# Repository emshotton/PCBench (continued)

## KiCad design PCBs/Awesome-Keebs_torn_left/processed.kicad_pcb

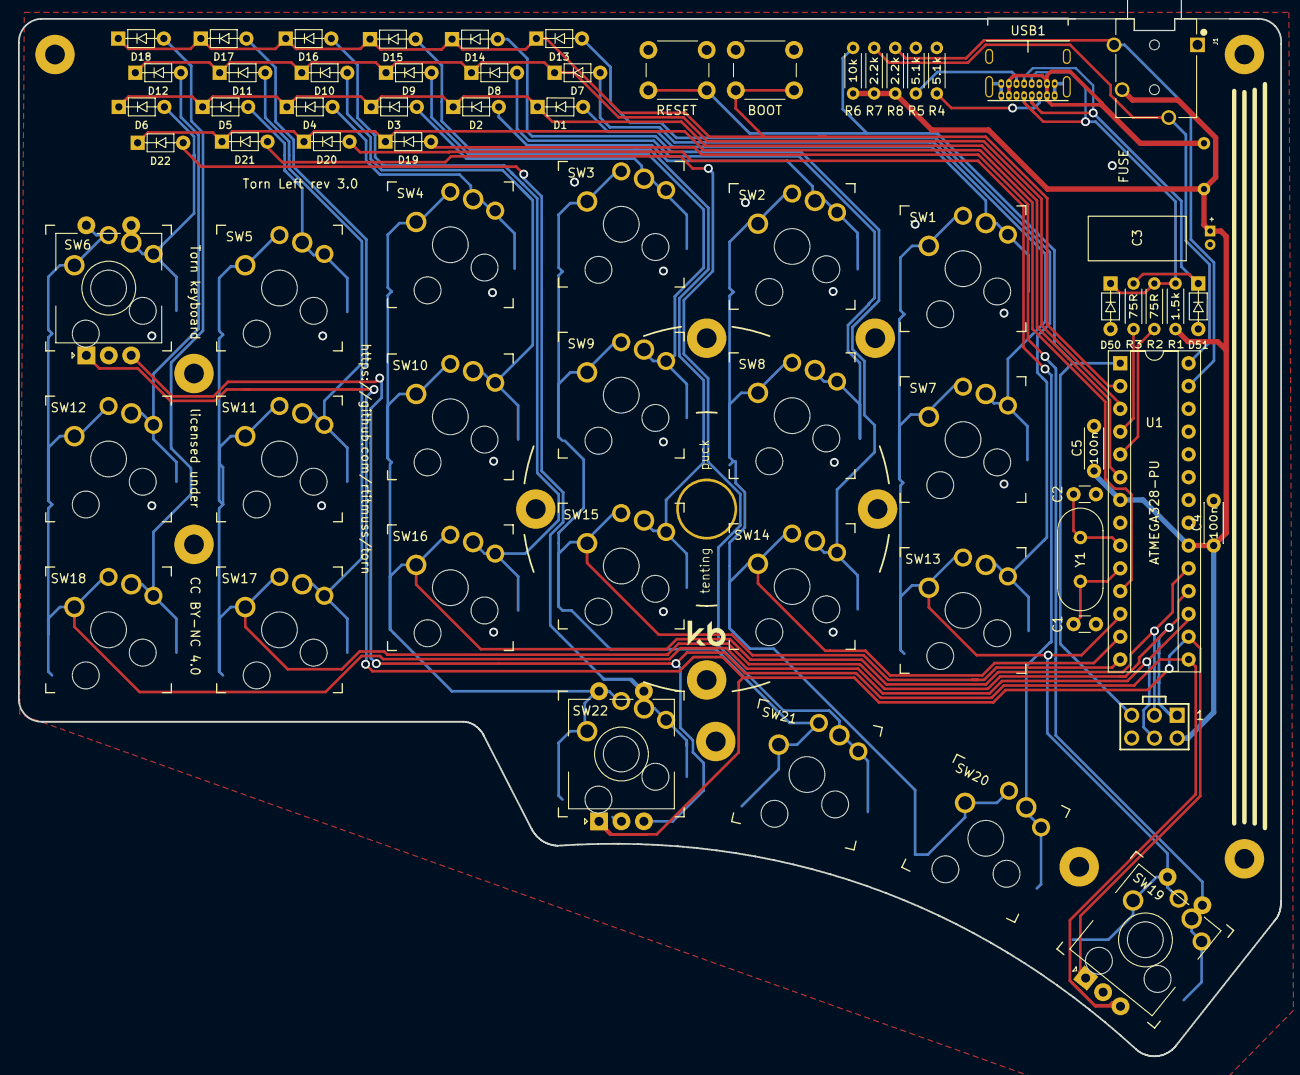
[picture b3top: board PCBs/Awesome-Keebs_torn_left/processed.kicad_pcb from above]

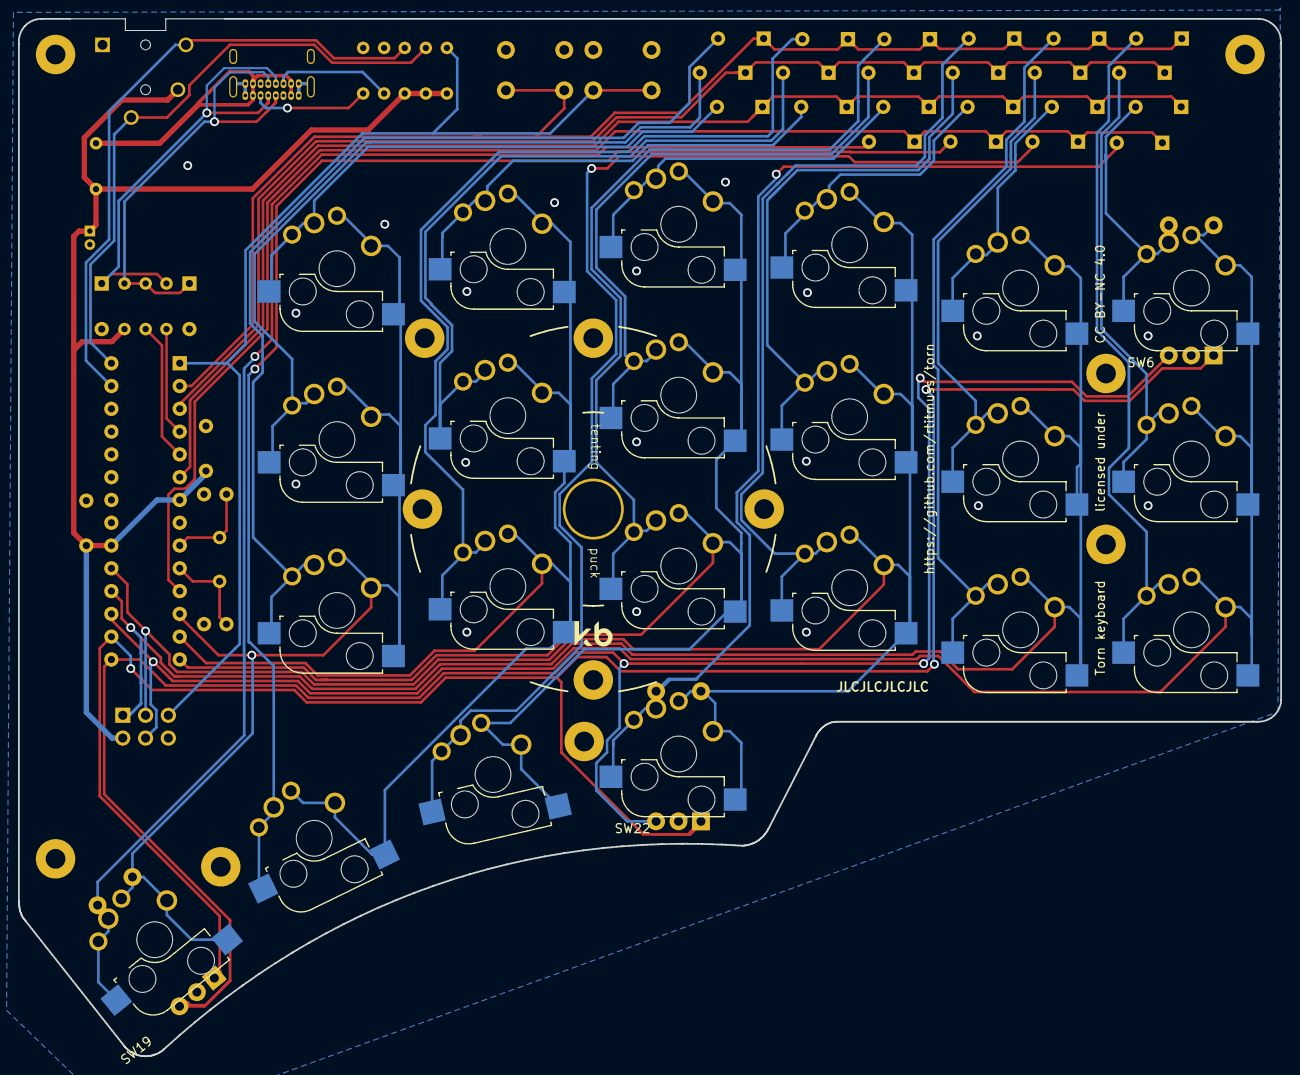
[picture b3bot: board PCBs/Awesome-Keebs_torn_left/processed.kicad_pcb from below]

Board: 2 copper layers, 140.7 x 115.6 mm, 76 parts (8 on the bottom side), 48 nets.

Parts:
C1, C2: 22p; C_Disc_D3.0mm_W1.6mm_P2.50mm
C3: 4.7u; CP_Radial_D4.0mm_P1.50mm
C4, C5: 100n; C_Disc_D4.3mm_W1.9mm_P5.00mm
D1, D2, D3, D4, D5, D6, D7, D8, D9, D10, D11, D12, D13, D14, D15, D16, D17, D18, D19, D20, D21, D22: 1N4148; D_DO-35_SOD27_P5.08mm_Horizontal
D50, D51: 3.6V; D_DO-35_SOD27_P5.08mm_Horizontal
F1: 100mA; polyfuse_5.1mm
H3, H4, H5, H6, H7, H8, H9, H10: M2; MountingHole_2.2mm_M2_Pad
ISP1: AVR_ISP_6; AVR_ICSP_3x2
J1: SJ-43514; CUI_SJ-43514
PB1: RESET; SW_PUSH_6mm
PB2: BOOT; SW_PUSH_6mm
PUCK1: SYM_Arrow45_Small; Tenting_Puck
R1: 1.5k; R_Axial_DIN0204_L3.6mm_D1.6mm_P5.08mm_Horizontal
R2, R3: 75R; R_Axial_DIN0204_L3.6mm_D1.6mm_P5.08mm_Horizontal
R4, R5: 5.1k; R_Axial_DIN0204_L3.6mm_D1.6mm_P5.08mm_Horizontal
R6: 10k; R_Axial_DIN0204_L3.6mm_D1.6mm_P5.08mm_Horizontal
R7, R8: 2.2k; R_Axial_DIN0204_L3.6mm_D1.6mm_P5.08mm_Horizontal
SW1, SW2, SW3, SW4, SW5, SW7, SW8, SW9, SW10, SW11, SW12, SW13, SW14, SW15, SW16, SW17, SW18, SW20, SW21: SW_Push; Kailh_socket_MX_PG1350_optional
SW6, SW19, SW22: Rotary_Encoder_Switch; Kailh_socket_MX_PG1350_EC11_optional
U1: ATMEGA328-PU; DIP-28_W7.62mm_Socket
USB1: USB_C_GCT_USB4085-Type-C; USB_C_GCT_USB4085
Y1: 16MHz; Crystal_HC49-4H_Vertical

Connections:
+5V: C3.1, C4.1, C5.1, F1.2, ISP1.2, J1.2, R1.2, R6.1, R7.1, R8.1, U1.7, U1.20
/COL0: SW1.2, SW7.2, SW13.2, SW19.S2, U1.12
/COL1: SW2.2, SW8.2, SW14.2, SW20.2, U1.13
/COL2: SW3.2, SW9.2, SW15.2, SW21.2, U1.14
/COL3: ISP1.3, SW4.2, SW10.2, SW16.2, SW22.S2, U1.19
/COL4: ISP1.1, SW5.2, SW11.2, SW17.2, U1.18
/COL5: ISP1.4, SW6.S2, SW12.2, SW18.2, U1.17
/ENC0_A: SW6.A, SW19.A, SW22.A, U1.16
/ENC0_B: SW6.B, SW19.B, SW22.B, U1.15
/RESET: ISP1.5, PB1.1, R6.2, U1.1
/ROW0: D1.1, D2.1, D3.1, D4.1, D5.1, D6.1, U1.6
/ROW1: D7.1, D8.1, D9.1, D10.1, D11.1, D12.1, U1.3
/ROW2: D13.1, D14.1, D15.1, D16.1, D17.1, D18.1, PB2.2, U1.2
/ROW3: D19.1, D20.1, D21.1, D22.1, U1.11
/USB_D+: R3.1, U1.4
/USB_D-: R2.1, U1.5
/i2c_SCL: J1.3, R7.2, U1.28
/i2c_SDA: J1.4, R8.2, U1.27
GND: C1.2, C2.2, C3.2, C4.2, C5.2, D50.2, D51.2, ISP1.6, J1.1, PB1.2, PB2.1, R4.1, R5.1, SW6.C, SW19.C, SW22.C, U1.8, U1.22, USB1.A1, USB1.A12, USB1.B1, USB1.B12, USB1.S1
unnamed: C1.1, U1.10, Y1.2
unnamed: C2.1, U1.9, Y1.1
unnamed: D1.2, SW1.1
unnamed: D2.2, SW2.1
unnamed: D3.2, SW3.1
unnamed: D4.2, SW4.1
unnamed: D5.2, SW5.1
unnamed: D6.2, SW6.S1
unnamed: D7.2, SW7.1
unnamed: D8.2, SW8.1
unnamed: D9.2, SW9.1
unnamed: D10.2, SW10.1
unnamed: D11.2, SW11.1
unnamed: D12.2, SW12.1
unnamed: D13.2, SW13.1
unnamed: D14.2, SW14.1
unnamed: D15.2, SW15.1
unnamed: D16.2, SW16.1
unnamed: D17.2, SW17.1
unnamed: D18.2, SW18.1
unnamed: D19.2, SW19.S1
unnamed: D20.2, SW20.1
unnamed: D21.2, SW21.1
unnamed: D22.2, SW22.S1
unnamed: D50.1, R1.1, R2.2, USB1.A7, USB1.B7
unnamed: D51.1, R3.2, USB1.A6, USB1.B6
unnamed: F1.1, USB1.A4, USB1.A9, USB1.B4, USB1.B9
unnamed: R4.2, USB1.A5
unnamed: R5.2, USB1.B5

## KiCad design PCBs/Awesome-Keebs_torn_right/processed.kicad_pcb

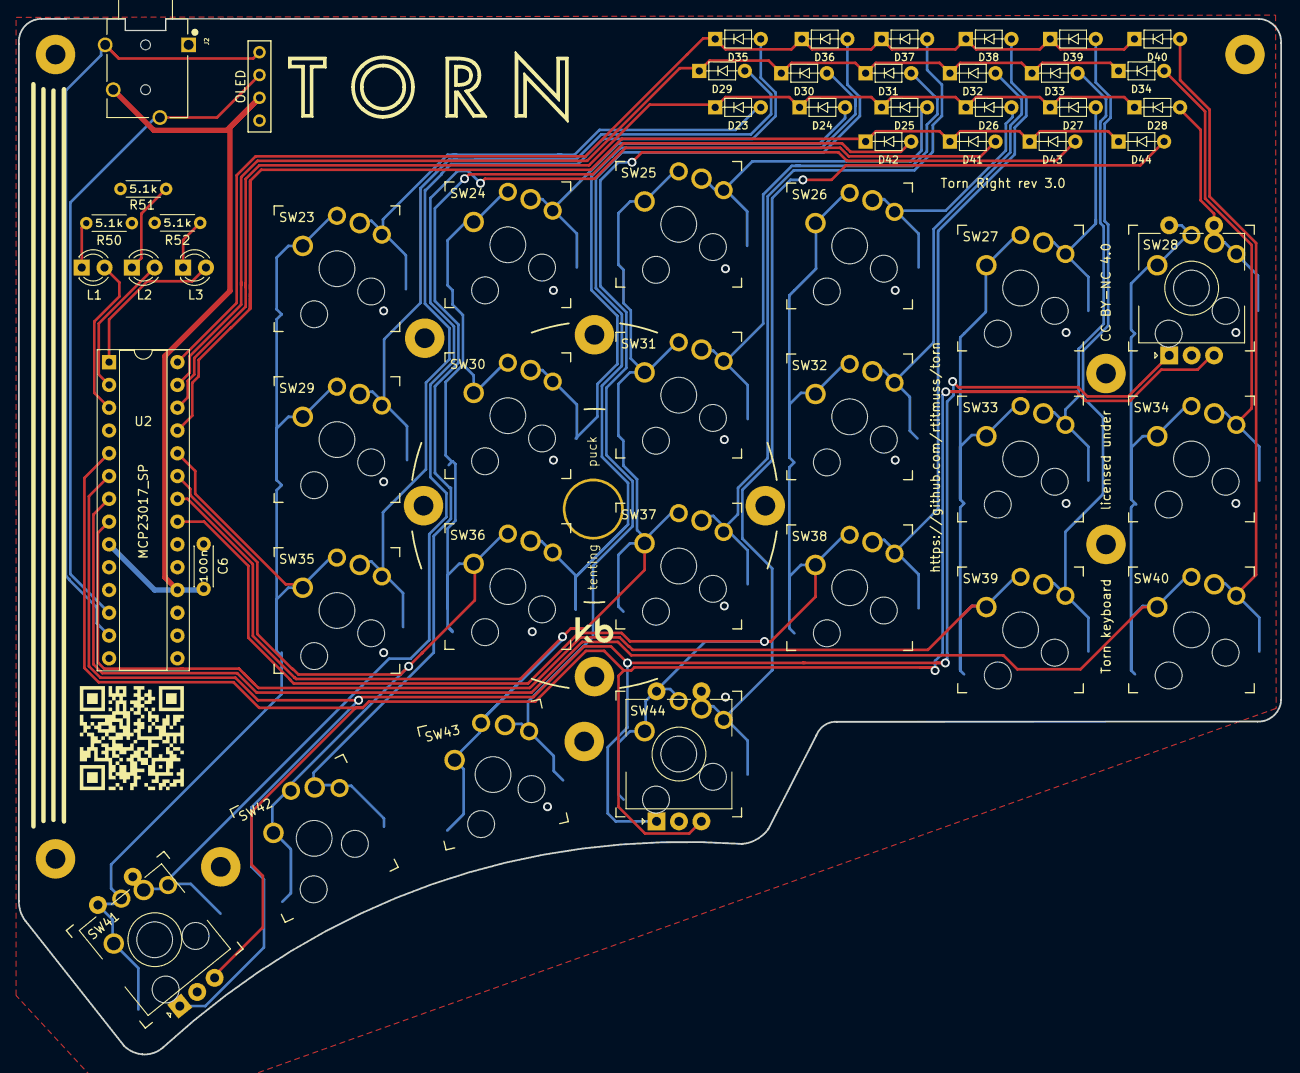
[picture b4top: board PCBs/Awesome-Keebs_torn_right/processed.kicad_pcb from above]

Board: 2 copper layers, 140.7 x 115.4 mm, 64 parts (0 on the bottom side), 44 nets.

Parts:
C6: 100n; C_Disc_D4.3mm_W1.9mm_P5.00mm
D23, D24, D25, D26, D27, D28, D29, D30, D31, D32, D33, D34, D35, D36, D37, D38, D39, D40, D41, D42, D43, D44: 1N4148; D_DO-35_SOD27_P5.08mm_Horizontal
H3, H4, H5, H6, H7, H8, H9, H10: M2; MountingHole_2.2mm_M2_Pad
J2: SJ-43514; CUI_SJ-43514
J3: Conn_01x04; OLED_1side
L1, L2, L3: LED; LED_D3.0mm
PUCK1: PUCK; Tenting_Puck
QR1: SYM_Arrow45_Small; torn_qr_code
R50, R51, R52: 5.1k; R_Axial_DIN0204_L3.6mm_D1.6mm_P5.08mm_Horizontal
SW23, SW24, SW25, SW26, SW27, SW29, SW30, SW31, SW32, SW33, SW34, SW35, SW36, SW37, SW38, SW39, SW40, SW42, SW43: SW_Push; Kailh_socket_MX_PG1350_optional
SW28, SW41, SW44: Rotary_Encoder_Switch; Kailh_socket_MX_PG1350_EC11_optional
U2: MCP23017_SP; DIP-28_W7.62mm_Socket

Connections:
+5V: C6.1, J2.2, J3.2, U2.9, U2.18
/COL6: SW23.2, SW29.2, SW35.2, SW41.S2, U2.24
/COL7: SW24.2, SW30.2, SW36.2, SW42.2, U2.23
/COL8: SW25.2, SW31.2, SW37.2, SW43.2, U2.22
/COL9: SW26.2, SW32.2, SW38.2, SW44.S2, U2.21
/COL10: SW27.2, SW33.2, SW39.2, U2.8
/COL11: SW28.S2, SW34.2, SW40.2, U2.7
/ENC1_A: SW28.A, SW41.A, SW44.A, U2.6
/ENC1_B: SW28.B, SW41.B, SW44.B, U2.5
/LED1: L1.2, U2.3
/LED2: L2.2, U2.2
/LED3: L3.2, U2.1
/ROW0: D23.1, D24.1, D25.1, D26.1, D27.1, D28.1, U2.26
/ROW1: D29.1, D30.1, D31.1, D32.1, D33.1, D34.1, U2.27
/ROW2: D35.1, D36.1, D37.1, D38.1, D39.1, D40.1, U2.28
/ROW3: D41.1, D42.1, D43.1, D44.1, U2.25
/i2c_SCL: J2.3, J3.3, U2.12
/i2c_SDA: J2.4, J3.4, U2.13
GND: C6.2, J2.1, J3.1, R50.1, R51.1, R52.1, SW28.C, SW41.C, SW44.C, U2.10, U2.15, U2.16, U2.17
unnamed: D23.2, SW23.1
unnamed: D24.2, SW24.1
unnamed: D25.2, SW25.1
unnamed: D26.2, SW26.1
unnamed: D27.2, SW27.1
unnamed: D28.2, SW28.S1
unnamed: D29.2, SW29.1
unnamed: D30.2, SW30.1
unnamed: D31.2, SW31.1
unnamed: D32.2, SW32.1
unnamed: D33.2, SW33.1
unnamed: D34.2, SW34.1
unnamed: D35.2, SW35.1
unnamed: D36.2, SW36.1
unnamed: D37.2, SW37.1
unnamed: D38.2, SW38.1
unnamed: D39.2, SW39.1
unnamed: D40.2, SW40.1
unnamed: D41.2, SW41.S1
unnamed: D42.2, SW42.1
unnamed: D43.2, SW43.1
unnamed: D44.2, SW44.S1
unnamed: L1.1, R50.2
unnamed: L2.1, R51.2
unnamed: L3.1, R52.2

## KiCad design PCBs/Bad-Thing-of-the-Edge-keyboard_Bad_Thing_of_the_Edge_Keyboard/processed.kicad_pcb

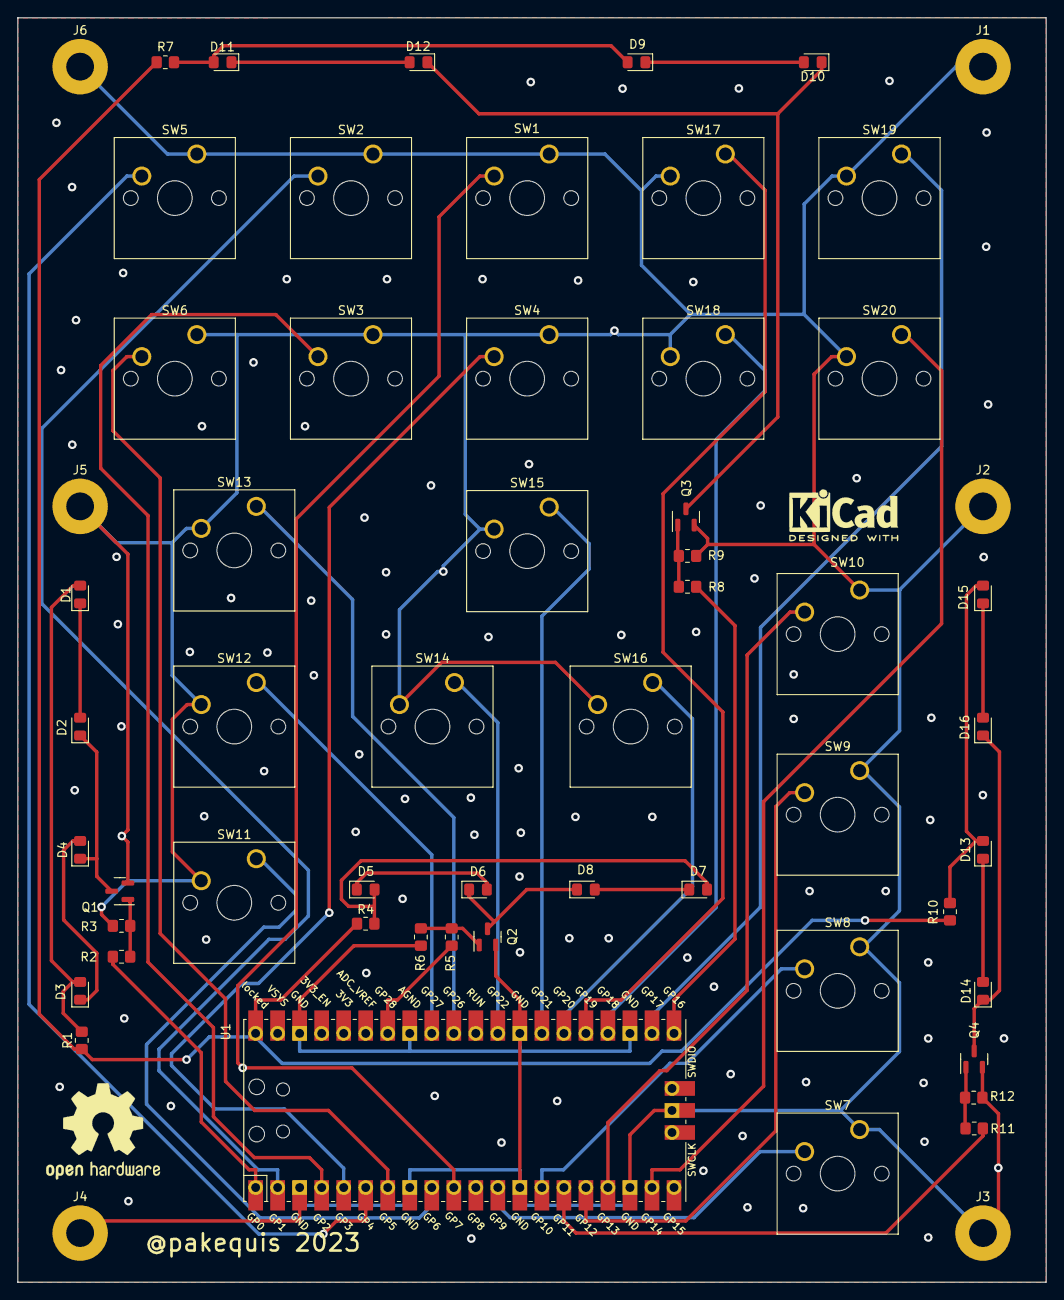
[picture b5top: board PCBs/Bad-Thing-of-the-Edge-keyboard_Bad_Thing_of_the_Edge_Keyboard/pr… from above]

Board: 2 copper layers, 118.6 x 145.8 mm, 61 parts (0 on the bottom side), 46 nets.

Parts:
D1, D2, D3, D4, D5, D6, D7, D8, D9, D10, D11, D12, D13, D14, D15, D16: LED; LED_0805_2012Metric_Pad1.15x1.40mm_HandSolder
J1, J2, J3, J4, J5, J6: Conn_01x01_Pin; MountingHole_3.2mm_M3_Pad
Q1, Q2, Q3, Q4: BSS138; SOT-23
R1, R4, R7, R10: 47R; R_0805_2012Metric_Pad1.20x1.40mm_HandSolder
R2, R5, R8, R11: 100R; R_0805_2012Metric_Pad1.20x1.40mm_HandSolder
R3, R6, R9, R12: 10k; R_0805_2012Metric_Pad1.20x1.40mm_HandSolder
SW1, SW2, SW3, SW4, SW5, SW6, SW7, SW8, SW9, SW10, SW11, SW12, SW13, SW14, SW15, SW16, SW17, SW18, SW19, SW20: SW_Push; SW_Cherry_MX_1.00u_PCB
U1: Pico; RPi_Pico_SMD_TH
m1: OSHW-Logo2_14.6x12mm_SilkScreen
m2: KiCad-Logo2_5mm_SilkScreen

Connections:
GNDREF: J1.1, J2.1, J3.1, J4.1, J5.1, J6.1, Q1.2 (S), Q2.2 (S), Q3.2 (S), Q4.2 (S), R3.2, R6.2, R9.2, R12.2, SW1.1, SW2.1, SW3.1, SW4.1, SW5.1, SW6.1, SW7.1, SW8.1, SW9.1, SW10.1, SW11.2, SW12.2, SW13.2, SW14.2, SW15.2, SW16.2, SW17.2, SW18.2, SW19.2, SW20.2, U1.3 (GND), U1.8 (GND), U1.13 (GND), U1.18 (GND), U1.23 (GND), U1.28 (GND), U1.33 (AGND), U1.38 (GND), U1.42 (GND)
unnamed: D1.2 (A), D3.2 (A), R1.2
unnamed: D1.1 (K), D2.2 (A)
unnamed: D2.1 (K), D4.1 (K), Q1.3 (D)
unnamed: D3.1 (K), D4.2 (A)
unnamed: D5.2 (A), D7.2 (A), R4.2
unnamed: D5.1 (K), D6.2 (A)
unnamed: D6.1 (K), D8.1 (K), Q2.3 (D)
unnamed: D7.1 (K), D8.2 (A)
unnamed: D9.1 (K), D10.2 (A)
unnamed: D10.1 (K), D12.1 (K), Q3.3 (D)
unnamed: D9.2 (A), D11.2 (A), R7.2
unnamed: D11.1 (K), D12.2 (A)
unnamed: D13.2 (A), D15.2 (A), R10.2
unnamed: D13.1 (K), D14.2 (A)
unnamed: D14.1 (K), D16.1 (K), Q4.3 (D)
unnamed: D15.1 (K), D16.2 (A)
unnamed: Q1.1 (G), R2.2, R3.1
unnamed: Q2.1 (G), R5.2, R6.1
unnamed: Q3.1 (G), R8.2, R9.1
unnamed: Q4.1 (G), R11.2, R12.1
unnamed: R2.1, U1.1 (GPIO0)
unnamed: SW2.2, U1.2 (GPIO1)
unnamed: SW3.2, U1.4 (GPIO2)
unnamed: SW4.2, U1.5 (GPIO3)
unnamed: SW5.2, U1.6 (GPIO4)
unnamed: SW6.2, U1.7 (GPIO5)
unnamed: SW11.1, U1.9 (GPIO6)
unnamed: SW1.2, U1.10 (GPIO7)
unnamed: SW7.2, U1.12 (GPIO9)
unnamed: SW8.2, U1.14 (GPIO10)
unnamed: R11.1, U1.15 (GPIO11)
unnamed: SW9.2, U1.16 (GPIO12)
unnamed: SW10.2, U1.17 (GPIO13)
unnamed: SW20.1, U1.19 (GPIO14)
unnamed: R8.1, U1.21 (GPIO16)
unnamed: SW19.1, U1.22 (GPIO17)
unnamed: SW18.1, U1.24 (GPIO18)
unnamed: SW17.1, U1.25 (GPIO19)
unnamed: SW16.1, U1.26 (GPIO20)
unnamed: SW15.1, U1.27 (GPIO21)
unnamed: SW14.1, U1.29 (GPIO22)
unnamed: SW13.1, U1.31 (GPIO26_ADC0)
unnamed: SW12.1, U1.32 (GPIO27_ADC1)
unnamed: R5.1, U1.34 (GPIO28_ADC2)
VBUS: R1.1, R4.1, R7.1, R10.1, U1.40 (VBUS)

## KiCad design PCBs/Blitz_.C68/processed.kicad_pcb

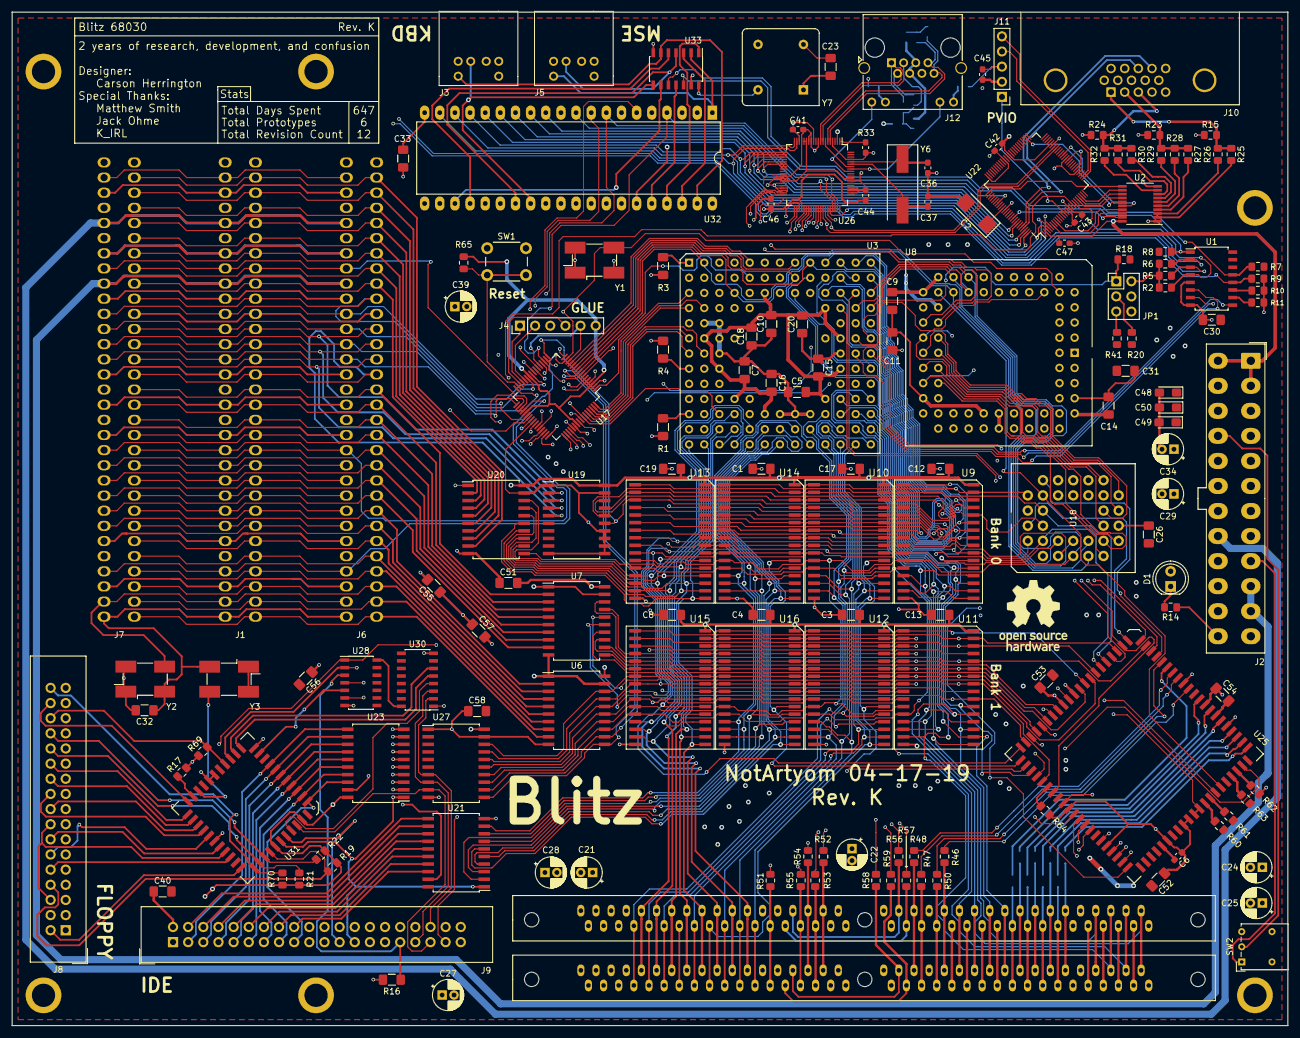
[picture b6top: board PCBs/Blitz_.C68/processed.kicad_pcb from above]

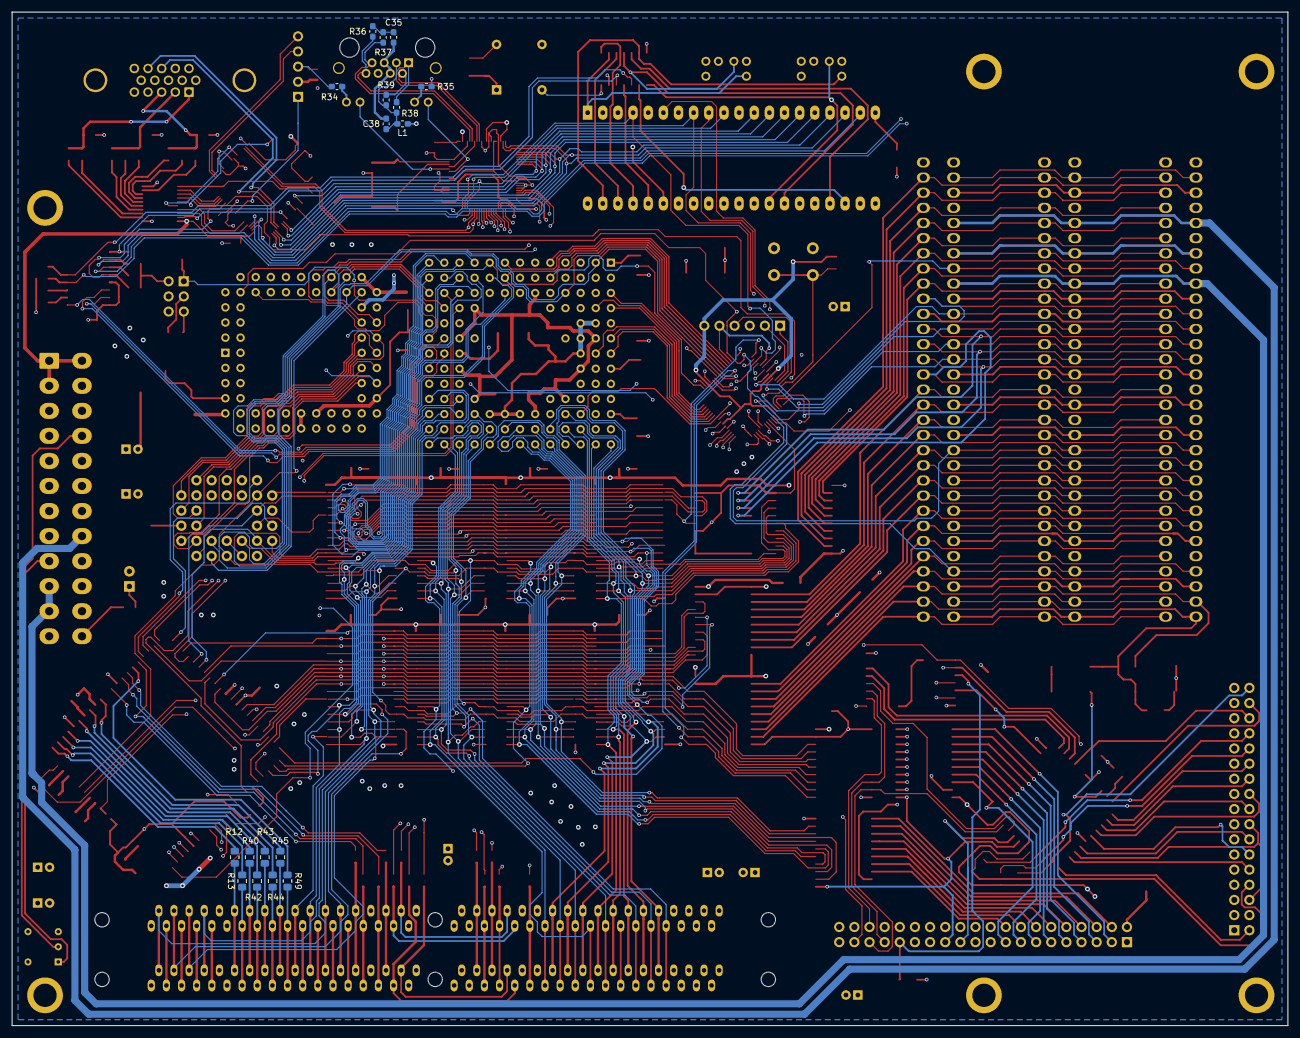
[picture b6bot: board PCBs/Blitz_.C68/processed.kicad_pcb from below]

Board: 4 copper layers, 214.0 x 170.0 mm, 184 parts (17 on the bottom side), 310 nets.

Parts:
C1, C3, C4, C5, C7, C8, C9, C10, C11, C12, C13, C14, C15, C16, C17, C18, C19, C20, C23, C26, C30, C31, C32, C33, C40, C51, C52, C53, C54, C55, C56, C57, C58: 100nf; C_1206_3216Metric_Pad1.42x1.75mm_HandSolder
C2: 10uf; CP_EIA-6032-20_AVX-F_Pad2.25x2.35mm_HandSolder
C6, C38, C41, C42, C43, C44, C45, C46, C47: 100nf; C_0603_1608Metric_Pad1.05x0.95mm_HandSolder
C21, C22, C24, C25, C27, C28, C29, C34: 47uf; CP_Radial_D5.0mm_P2.00mm
C35: 10nf; C_0603_1608Metric_Pad1.05x0.95mm_HandSolder
C36, C37: 10pf; C_0603_1608Metric_Pad1.05x0.95mm_HandSolder
C39: 10uf; CP_Radial_D5.0mm_P2.00mm
C48, C49, C50: 1uf; CP_EIA-3216-10_Kemet-I_Pad1.58x1.35mm_HandSolder
D1: LED; LED_D5.0mm
H1, H2, H3, H4, H5, H6: PTH_mount; atx_mounting_hole
J1, J6, J7: ISAx8; ISA_x8_VERT
J2: ATX24; Molex_Mini-Fit_Jr_5566-24A_2x12_P4.20mm_Vertical
J3: MSE; PS2
J4: PRG0; PinHeader_1x06_P2.54mm_Vertical
J5: KBD; PS2
J8: FLOPPY; IDC-Header_2x17_P2.54mm_Vertical
J9: IDE; IDC-Header_2x20_P2.54mm_Vertical
J10: VGA; Dsub-VGA
J11: ICSP; PinHeader_1x05_P2.54mm_Vertical
J12: RJ45_LED; RJ45_Amphenol_RJHSE538X
JP1: Conn_02x03_Odd_Even; PinHeader_2x03_P2.54mm_Vertical
L1: L; L_0603_1608Metric_Pad1.05x0.95mm_HandSolder
R1, R3, R4, R16: 10k; R_1206_3216Metric_Pad1.42x1.75mm_HandSolder
R2, R5, R6, R7, R8, R9, R10, R11, R14, R18, R20, R41, R65: 10k; R_0805_2012Metric_Pad1.15x1.40mm_HandSolder
R12, R13, R40, R42, R43, R44, R45, R46, R47, R48, R49, R50, R51, R52, R53, R54, R55, R56, R57, R58, R59: 22; R_0805_2012Metric_Pad1.15x1.40mm_HandSolder
R15, R23, R24: 75; R_0805_2012Metric_Pad1.15x1.40mm_HandSolder
R17, R19, R21, R22, R69, R70: 150; R_0805_2012Metric_Pad1.15x1.40mm_HandSolder
R25: 455; R_0805_2012Metric_Pad1.15x1.40mm_HandSolder
R26: 986; R_0805_2012Metric_Pad1.15x1.40mm_HandSolder
R27, R30: 544; R_0805_2012Metric_Pad1.15x1.40mm_HandSolder
R28, R31: 1k2; R_0805_2012Metric_Pad1.15x1.40mm_HandSolder
R29, R32: 2k4; R_0805_2012Metric_Pad1.15x1.40mm_HandSolder
R33: 12.3k; R_0603_1608Metric_Pad1.05x0.95mm_HandSolder
R34, R35: 330; R_0603_1608Metric_Pad1.05x0.95mm_HandSolder
R36, R37, R38, R39: 49k9; R_0603_1608Metric_Pad1.05x0.95mm_HandSolder
R60, R61, R62, R63, R64: 2k2; R_0805_2012Metric_Pad1.15x1.40mm_HandSolder
SW1: RESET; SW_PUSH_6mm
SW2: SW_SPDT; SW_Lever_1P2T_NKK_GW12LxH
U1: 74LS148; SOIC-16W_5.3x10.2mm_P1.27mm
U2: 74LVC245APW; TSSOP-20_4.4x6.5mm_P0.65mm
U3: M68030; PGA120
U5, U24: SIMM_72
U6, U7, U19, U20, U21, U23, U27: 74LS245; SOIC-20W_7.5x12.8mm_P1.27mm
U8: M68882_PLCC; PLCC-68_THT-Socket
U9, U10, U11, U12, U13, U14, U15, U16: AS6C4008; SOIC-32
U17: XC9572XL-VQ64; TQFP-64_10x10mm_P0.5mm
U18: SST39SF040; PLCC-32_TH
U22: PIC24FJ256DA210-IPT; TQFP-100_12x12mm_P0.4mm
U25: DP8440; PLCC-84
U26: W5100; LQFP-80_10x10mm_P0.4mm
U28: 7404; SOIC-14_3.9x8.7mm_P1.27mm
U30: 74hc139; SOIC-16_3.9x9.9mm_P1.27mm
U31: WD37C65; PLCC-44
U32: 8042; DIP-40_W15.24mm_LongPads
U33: 74LS06; SOIC-14_3.9x8.7mm_P1.27mm
Y1: 20MHz; Oscillator_SMD_EuroQuartz_XO91-4Pin_7.0x5.0mm_HandSoldering
Y2: 14.316MHz; Oscillator_SMD_EuroQuartz_XO91-4Pin_7.0x5.0mm_HandSoldering
Y3: 16MHz; Oscillator_SMD_EuroQuartz_XO91-4Pin_7.0x5.0mm_HandSoldering
Y6: 25MHz; Crystal_SMD_HC49-SD
Y7: 8MHz; Oscillator_DIP-8

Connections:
!READ: J9.25, U17.56, U18.24, U21.1, U23.1, U26.58, U31.1, U32.8
+3V3: C41.2, C42.2, C43.2, C44.2, C45.2, C46.2, C47.2, J2.1, J2.2, J2.12, J2.13, J4.6, J11.2, L1.2, R65.1, U2.20, U17.3, U17.26, U17.37, U17.55, U22.2, U22.16, U22.30, U22.37, U22.46, U22.62, U22.86, U26.2, U26.12, U26.18, U26.44
+5V: C1.2, C3.2, C4.2, C5.2, C7.2, C8.2, C9.2, C10.2, C11.2, C12.2, C13.2, C14.2, C15.2, C16.2, C17.2, C18.2, C19.2, C20.2, C21.1, C22.1, C23.2, C24.1, C25.1, C26.2, C27.1, C28.1, C29.1, C30.2, C31.2, C32.2, C33.2, C34.1, C39.1, C40.2, C48.1, C49.1, C50.1, C51.2, C52.2, C53.2, C54.2, C55.2, C56.2, C57.2, C58.2, D1.2, J1.B3, J1.B15, J1.B17, J1.B19, J1.B26, J1.B29, J2.4, J2.6, J2.21, J2.22, J2.23, J3.4, J5.4, J6.B3, J6.B15, J6.B17, J6.B19, J6.B26, J6.B29, J7.B3, J7.B15, J7.B17, J7.B19, J7.B26, J7.B29, J9.29, J9.38, R1.1, R3.1, R4.1, R7.1, R8.1, R17.2, R18.1, R19.2, R20.1, R21.2, R22.2, R41.1, R60.1, R61.1, R63.1, R69.2, R70.2, U1.16, U3.C6, U3.D4, U3.D10, U3.F2, U3.F11, U3.H3, U3.H11, U3.K4, U3.K10, U3.L6, U5.10, U5.30, U5.59, U6.20, U7.20, U8.10, U8.16, U8.17, U8.18, U8.26, U8.27, U8.43, U8.52, U8.53, U8.61, U9.32, U10.32, U11.32, U12.32, U13.32, U14.32, U15.32, U16.32, U18.32, U19.20, U20.20, U21.20, U23.20, U24.10, U24.30, U24.59, U25.1, U25.22, U25.40, U25.47, U25.57, U25.61, U25.81, U27.20, U28.14, U30.16, U31.5, U31.44, U32.5, U32.25, U32.26, U32.40, U33.14, Y1.1, Y1.4, Y2.1, Y2.4, Y3.1, Y3.4, Y7.1, Y7.8
+12V: J1.B9, J2.10, J2.11, J6.B9, J7.B9
-5V: J1.B5, J2.20, J6.B5, J7.B5
-12V: J1.B7, J2.14, J6.B7, J7.B7
/A0: U3.A2, U6.11, U17.8, U18.12, U22.44, U26.54, U27.11, U32.9
/A1: U3.C4, U6.12, U8.25, U17.9, U18.11, U22.43, U26.53, U27.12
/A2: U3.D13, U6.13, U8.24, U9.12, U10.12, U11.12, U12.12, U13.12, U14.12, U15.12, U16.12, U18.10, U25.9, U26.52, U27.13
/A3: U3.D12, U6.14, U8.23, U9.11, U10.11, U11.11, U12.11, U13.11, U14.11, U15.11, U16.11, U18.9, U25.11, U26.51, U27.14
/A4: U3.C13, U6.15, U8.22, U9.10, U10.10, U11.10, U12.10, U13.10, U14.10, U15.10, U16.10, U18.8, U25.13, U25.39, U26.50, U27.15
/A5: U3.C12, U6.16, U9.9, U10.9, U11.9, U12.9, U13.9, U14.9, U15.9, U16.9, U18.7, U25.15, U26.49, U27.16
/A6: U3.D11, U6.17, U9.8, U10.8, U11.8, U12.8, U13.8, U14.8, U15.8, U16.8, U18.6, U25.17, U26.48, U27.17
/A7: U3.B13, U6.18, U9.7, U10.7, U11.7, U12.7, U13.7, U14.7, U15.7, U16.7, U18.5, U25.19, U26.47, U27.18
/A8: U3.B12, U7.11, U9.6, U10.6, U11.6, U12.6, U13.6, U14.6, U15.6, U16.6, U18.27, U25.21, U26.46
/A9: U3.C11, U7.12, U9.5, U10.5, U11.5, U12.5, U13.5, U14.5, U15.5, U16.5, U18.26, U25.25, U26.45
/A10: U3.A13, U7.13, U9.27, U10.27, U11.27, U12.27, U13.27, U14.27, U15.27, U16.27, U18.23, U25.27, U26.42
/A11: U3.C10, U7.14, U9.26, U10.26, U11.26, U12.26, U13.26, U14.26, U15.26, U16.26, U18.25, U25.29, U26.41
/A12: U3.B11, U7.15, U9.23, U10.23, U11.23, U12.23, U13.23, U14.23, U15.23, U16.23, U18.4, U25.31, U26.40
/A13: U3.A12, U7.16, U9.25, U10.25, U11.25, U12.25, U13.25, U14.25, U15.25, U16.25, U18.28, U25.37, U26.39
/A14: U3.B10, U7.17, U9.4, U10.4, U11.4, U12.4, U13.4, U14.4, U15.4, U16.4, U18.29, U25.8, U26.38
/A15: U3.A11, U7.18, U9.28, U10.28, U11.28, U12.28, U13.28, U14.28, U15.28, U16.28, U18.3, U25.10
/A16: U3.B9, U9.3, U10.3, U11.3, U12.3, U13.3, U14.3, U15.3, U16.3, U17.17, U18.2, U19.15, U25.12
/A17: U3.A10, U9.31, U10.31, U11.31, U12.31, U13.31, U14.31, U15.31, U16.31, U18.30, U19.16, U25.14
/A18: U3.C8, U9.2, U10.2, U11.2, U12.2, U13.2, U14.2, U15.2, U16.2, U18.1, U19.17, U25.16
/A19: U3.A9, U9.30, U10.30, U11.30, U12.30, U13.30, U14.30, U15.30, U16.30, U17.10, U19.18, U25.18
/A20: U3.B8, U9.1, U10.1, U11.1, U12.1, U13.1, U14.1, U15.1, U16.1, U17.11, U25.20
/A21: U3.A8, U17.12, U25.23
/A22: U3.B7, U25.26
/A23: U3.A7, U25.28
/A24: U3.A6, U25.30
/A25: U3.B6, U25.36
/A26: U3.A5, U17.13
/A27: U3.B5, U17.1
/B0: R30.2, U2.7
/B1: R31.2, U2.8
/B2: R32.2, U2.9
/CAS0: R52.1, U5.40, U24.40
/CAS1: R53.1, U5.41, U24.41
/CAS2: R54.1, U5.42, U24.42
/CAS3: R55.1, U5.43, U24.43
/D0: U3.K13, U5.2, U8.3, U9.13, U11.13, U24.2
/D1: U3.K12, U5.4, U8.2, U9.14, U11.14, U24.4
/D2: U3.L13, U5.6, U8.1, U9.15, U11.15, U24.6
/D3: U3.M13, U5.8, U8.68, U9.17, U11.17, U24.8
/D4: U3.L12, U5.20, U8.67, U9.18, U11.18, U24.20
/D5: U3.K11, U5.22, U8.66, U9.19, U11.19, U24.22
/D6: U3.M12, U5.24, U8.65, U9.20, U11.20, U24.24
/D7: U3.L11, U5.26, U8.64, U9.21, U11.21, U24.26
/D8: U3.N13, U5.49, U8.62, U10.13, U12.13, U24.49
/D9: U3.M11, U5.51, U8.60, U10.14, U12.14, U24.51
/D10: U3.L10, U5.53, U8.59, U10.15, U12.15, U24.53
/D11: U3.N12, U5.55, U8.58, U10.17, U12.17, U24.55
/D12: U3.M10, U5.57, U8.57, U10.18, U12.18, U24.57
/D13: U3.N11, U5.61, U8.56, U10.19, U12.19, U24.61
/D14: U3.M9, U5.63, U8.55, U10.20, U12.20, U24.63
/D15: U3.N10, U5.65, U8.54, U10.21, U12.21, U24.65
/D16: U3.N9, U5.3, U8.50, U14.13, U16.13, U21.9, U24.3
/D17: U3.M8, U5.5, U8.49, U14.14, U16.14, U21.8, U24.5
/D18: U3.N8, U5.7, U8.48, U14.15, U16.15, U21.7, U24.7
/D19: U3.N7, U5.9, U8.47, U14.17, U16.17, U21.6, U24.9
/D20: U3.M7, U5.21, U8.46, U14.18, U16.18, U21.5, U24.21
/D21: U3.N6, U5.23, U8.45, U14.19, U16.19, U21.4, U24.23
/D22: U3.M6, U5.25, U8.44, U14.20, U16.20, U21.3, U24.25
/D23: U3.N5, U5.27, U8.42, U14.21, U16.21, U21.2, U24.27
/D24: U3.M5, U5.50, U8.40, U13.13, U15.13, U18.13, U20.18, U22.93, U23.2, U24.50, U26.26, U32.12
/D25: U3.N4, U5.52, U8.39, U13.14, U15.14, U18.14, U20.17, U22.94, U23.3, U24.52, U26.25, U32.13
/D26: U3.N3, U5.54, U8.38, U13.15, U15.15, U18.15, U20.16, U22.98, U23.4, U24.54, U26.24, U32.14
/D27: U3.M4, U5.56, U8.37, U13.17, U15.17, U18.17, U20.15, U22.99, U23.5, U24.56, U26.23, U32.15
/D28: U3.N2, U5.58, U8.36, U13.18, U15.18, U18.18, U20.14, U22.100, U23.6, U24.58, U26.22, U32.16
/D29: U3.M3, U5.60, U8.35, U13.19, U15.19, U18.19, U20.13, U22.3, U23.7, U24.60, U26.21, U32.17
/D30: U3.L4, U5.62, U8.34, U13.20, U15.20, U18.20, U20.12, U22.4, U23.8, U24.62, U26.20, U32.18
/D31: U3.N1, U5.64, U8.33, U13.21, U15.21, U18.21, U20.11, U22.5, U23.9, U24.64, U26.19, U32.19
/G0: R27.2, U2.4
/G1: R28.2, U2.5
/G2: R29.2, U2.6
/IA0: J1.A31, J6.A31, J7.A31, U6.9
/IA1: J1.A30, J6.A30, J7.A30, U6.8
/IA2: J1.A29, J6.A29, J7.A29, U6.7
/IA3: J1.A28, J6.A28, J7.A28, U6.6
/IA4: J1.A27, J6.A27, J7.A27, U6.5
/IA5: J1.A26, J6.A26, J7.A26, U6.4
/IA6: J1.A25, J6.A25, J7.A25, U6.3
/IA7: J1.A24, J6.A24, J7.A24, U6.2
/IA8: J1.A23, J6.A23, J7.A23, U7.9
/IA9: J1.A22, J6.A22, J7.A22, U7.8
/IA10: J1.A21, J6.A21, J7.A21, U7.7
/IA11: J1.A20, J6.A20, J7.A20, U7.6
/IA12: J1.A19, J6.A19, J7.A19, U7.5
/IA13: J1.A18, J6.A18, J7.A18, U7.4
/IA14: J1.A17, J6.A17, J7.A17, U7.3
/IA15: J1.A16, J6.A16, J7.A16, U7.2
/IA16: J1.A15, J6.A15, J7.A15, U19.5
/IA17: J1.A14, J6.A14, J7.A14, U19.4
/IA18: J1.A13, J6.A13, J7.A13, U19.3
/IA19: J1.A12, J6.A12, J7.A12, U19.2
/ID0: J1.A9, J6.A9, J7.A9, U20.2
/ID1: J1.A8, J6.A8, J7.A8, U20.3
/ID2: J1.A7, J6.A7, J7.A7, U20.4
/ID3: J1.A6, J6.A6, J7.A6, U20.5
/ID4: J1.A5, J6.A5, J7.A5, U20.6
/ID5: J1.A4, J6.A4, J7.A4, U20.7
/ID6: J1.A3, J6.A3, J7.A3, U20.8
/ID7: J1.A2, J6.A2, J7.A2, U20.9
/IOA0: J9.35, U27.9, U31.4
/IOA1: J9.33, U27.8, U30.3
/IOA2: J9.36, U27.7, U30.2
/IOD16: J9.4, U21.11
/IOD17: J9.6, U21.12
/IOD18: J9.8, U21.13
/IOD19: J9.10, U21.14
/IOD20: J9.12, U21.15
/IOD21: J9.14, U21.16
/IOD22: J9.16, U21.17
/IOD23: J9.18, U21.18
/IOD24: J9.17, U23.18, U31.7
/IOD25: J9.15, U23.17, U31.8
/IOD26: J9.13, U23.16, U31.9
/IOD27: J9.11, U23.15, U31.10
/IOD28: J9.9, U23.14, U31.11
/IOD29: J9.7, U23.13, U31.12
/IOD30: J9.5, U23.12, U31.13
/IOD31: J9.3, U23.11, U31.14
/QA0: R12.1, U5.12, U24.12
/QA1: R13.1, U5.13, U24.13
/QA2: R40.1, U5.14, U24.14
/QA3: R42.1, U5.15, U24.15
/QA4: R43.1, U5.16, U24.16
/QA5: R44.1, U5.17, U24.17
/QA6: R45.1, U5.18, U24.18
/QA7: R46.1, U5.28, U24.28
/QA8: R47.1, U5.31, U24.31
/QA9: R48.1, U5.32, U24.32
/QA10: R49.1, U5.19, U24.19
/QA11: R50.1, U5.29, U24.29
/R0: R25.2, U2.2
/R1: R26.2, U2.3
/RAS0: R56.1, U5.34, U5.44
/RAS1: R57.1, U5.33, U5.45
/RAS2: R58.1, U24.34, U24.44
/RAS3: R59.1, U24.33, U24.45
/RXI+: J12.7, R37.2, U26.5
/RXI-: J12.8, R36.1, U26.6
/TXO+: J12.1, R38.2, U26.8
/TXO-: J12.2, R39.1, U26.9
AS: U3.J2, U8.21, U17.2
BYTE0: U9.22, U11.22, U17.52, U25.35
BYTE1: U10.22, U12.22, U17.51, U25.34
BYTE2: U14.22, U16.22, U17.50, U25.33
BYTE3: U13.22, U15.22, U17.49, U25.32
CDIS: U3.H12, U17.23
CLK: J1.B20, J6.B20, J7.B20, U3.E1, U8.11, U17.15, U25.64, U25.65, Y1.3
DRAM_CS: U17.42, U25.53
DRAM_DTACK: U17.34, U25.73
DS: U3.K2, U8.20, U17.4
DSACK0: U3.F1, U8.31, U17.60
DSACK1: U3.G2, U8.32, U17.61
ECS: U3.M2, U17.18
ETHRNT: U17.43, U26.55
FC0: U3.D2, U17.63
FC1: U3.C1, U17.64
FC2: U3.D1, U17.62
FLOPPY: U17.20, U30.1
FPU: U8.29, U17.57
GEN: U2.19, U22.91
GND: C1.1, C2.2, C3.1, C4.1, C5.1, C6.1, C7.1, C8.1, C9.1, C10.1, C11.1, C12.1, C13.1, C14.1, C15.1, C16.1, C17.1, C18.1, C19.1, C20.1, C21.2, C22.2, C23.1, C24.2, C25.2, C26.1, C27.2, C28.2, C29.2, C30.1, C31.1, C32.1, C33.1, C34.2, C35.2, C36.2, C37.2, C38.2, C39.2, C40.1, C41.1, C42.1, C43.1, C44.1, C45.1, C46.1, C47.1, C48.2, C49.2, C50.2, C51.1, C52.1, C53.1, C54.1, C55.1, C56.1, C57.1, C58.1, H1.1, H2.1, H3.1, H4.1, H5.1, H6.1, J1.A11, J1.B1, J1.B10, J1.B31, J2.3, J2.5, J2.7, J2.15, J2.17, J2.18, J2.19, J2.24, J3.3, J4.5, J5.3, J6.A11, J6.B1, J6.B10, J6.B31, J7.A11, J7.B1, J7.B10, J7.B31, J8.1, J8.3, J8.5, J8.7, J8.9, J8.11, J8.13, J8.15, J8.17, J8.19, J8.21, J8.23, J8.25, J8.27, J8.29, J8.31, J8.33, J9.2, J9.19, J9.22, J9.24, J9.26, J9.28, J9.30, J9.40, J10.0, J10.5, J10.6, J10.7, J10.8, J10.10, J11.3, J12.4, J12.5, JP1.2, JP1.4, JP1.6, R2.1, R5.1, R6.1, R9.1, R10.1, R11.1, R14.1, R15.2, R16.1, R23.2, R24.2, R33.1, R34.1, R35.1, R62.1, R64.1, SW1.1, SW2.3, U1.5, U1.8, U2.1, U2.10, U3.C5, U3.C7, U3.C9, U3.E2, U3.E3, U3.E11, U3.F3, U3.G3, U3.G11, U3.J3, U3.J11, U3.L5, U3.L7, U3.L8, U3.L9, U5.1, U5.39, U5.72, U6.1, U6.10, U6.19, U7.1, U7.10, U7.19, U8.5, U8.6, U8.7, U8.8, U8.9, U8.12, U8.14, U8.19, U8.30, U8.41, U8.51, U8.63, U9.16, U10.16, U11.16, U12.16, U13.16, U14.16, U15.16, U16.16, U17.14, U17.21, U17.41, U17.54, U18.16, U19.1, U19.10, U19.11, U19.12, U19.13, U19.14, U19.19, U20.10, U20.19, U21.10, U22.15, U22.31, U22.36, U22.45, U22.65, U22.75, U23.10, U24.1, U24.39, U24.72, U25.3, U25.24, U25.42, U25.49, U25.59, U25.62, U25.63, U25.79, U25.83, U26.4, U26.10, U26.13, U26.14, U26.17, U26.31, U26.32, U26.34, U26.35, U26.36, U26.37, U26.43, U26.63, U26.64, U26.65, U26.68, U26.77, U27.1, U27.10, U27.19, U28.7, U30.8, U31.17, U31.23, U31.24, U31.34, U32.7, U32.20, U33.7, Y1.2, Y2.2, Y3.2, Y7.4
HALT: U3.H2, U17.16
ICSP_RES: J11.1, U22.13
IDE: J9.37, U17.7
IO_CS: U17.39, U21.19, U23.19
IPL0: U1.9, U3.H13
IPL1: U1.7, U3.G13
IPL2: U1.6, U3.G12
IRQ_ETH: R6.2, U1.2, U26.56
IRQ_FLOPPY: R5.2, U1.3, U28.6
IRQ_IDE: R9.2, U1.12, U28.4
IRQ_KBD: R8.2, U1.1, U33.12
IRQ_MSE: R7.2, U1.13, U33.10
IRQ_SYS: R2.2, U1.4, U22.19
ISA_IRQ0: J1.B25, J6.B25, J7.B25
ISA_IRQ1: J1.B24, J6.B24, J7.B24
ISA_IRQ2: J1.B23, J6.B23, J7.B23
ISA_IRQ3: J1.B22, J6.B22, J7.B22
ISA_IRQ4: J1.B21, J6.B21, J7.B21
I_DIR: U17.24, U20.1
KBD_CS: U17.22, U32.6
MMUDIS: JP1.1, R18.2, U3.F13
unnamed: C2.1, U22.85
unnamed: C6.2, U25.58
unnamed: C35.1, R36.2, R37.1
unnamed: C36.1, U26.76, Y6.1
unnamed: C37.1, U26.75, Y6.2
unnamed: C38.1, J12.3, L1.1, R38.1, R39.2
unnamed: D1.1, R14.2
unnamed: J1.A10, J6.A10, J7.A10, U17.38
unnamed: J1.B8, J6.B8, J7.B8, U17.35
unnamed: J1.B11, J6.B11, J7.B11, U17.25
unnamed: J1.B12, J6.B12, J7.B12, U17.27
unnamed: J1.B13, J6.B13, J7.B13, U17.32
unnamed: J1.B14, J6.B14, J7.B14, U17.33
unnamed: J1.B28, J6.B28, J7.B28, U17.36
unnamed: J1.B30, J6.B30, J7.B30, Y2.3
unnamed: J2.9, SW2.1
unnamed: J2.16, SW2.2
unnamed: J3.1, U32.28, U33.8
unnamed: J3.5, U32.39, U33.6
unnamed: J4.1, U17.29
unnamed: J4.2, U17.28
unnamed: J4.3, U17.53
unnamed: J4.4, U17.30
unnamed: J5.1, U32.27, U33.4
unnamed: J5.5, U32.1, U33.2
unnamed: J8.2, U31.39
unnamed: J8.8, R19.1, U31.43
unnamed: J8.10, U31.37
unnamed: J8.12, U31.33
unnamed: J8.14, U31.35
unnamed: J8.6, J8.16, U31.36
unnamed: J8.18, U31.31
unnamed: J8.20, U31.32
unnamed: J8.22, U31.30
unnamed: J8.24, U31.29
unnamed: J8.26, R21.1, U31.41
unnamed: J8.28, R22.1, U31.42
unnamed: J8.30, R69.1, U31.21
unnamed: J8.32, U31.28
unnamed: J8.34, R70.1, U31.40
unnamed: J9.31, R16.2, U28.3
unnamed: J10.1, R15.1, R25.1, R26.1
unnamed: J10.2, R23.1, R27.1, R28.1, R29.1
unnamed: J10.3, R24.1, R30.1, R31.1, R32.1
unnamed: J11.4, U22.27
unnamed: J11.5, U22.26
unnamed: J12.9, U26.72
unnamed: J12.10, R35.2
unnamed: J12.11, U26.73
unnamed: J12.12, R34.2
unnamed: JP1.3, R20.2
unnamed: JP1.5, R41.2
unnamed: R1.2, U3.L1
unnamed: R3.2, U3.A1
unnamed: R4.2, U3.H1
unnamed: R10.2, U1.11
unnamed: R11.2, U1.10
unnamed: R12.2, U25.75
unnamed: R13.2, U25.76
unnamed: R17.1, U31.27
unnamed: R33.2, U26.1
unnamed: R40.2, U25.77
unnamed: R42.2, U25.78
unnamed: R43.2, U25.80
unnamed: R44.2, U25.82
unnamed: R45.2, U25.84
unnamed: R46.2, U25.2
unnamed: R47.2, U25.4
unnamed: R48.2, U25.5
unnamed: R49.2, U25.6
unnamed: R50.2, U25.7
unnamed: R51.1, U5.47, U24.47
unnamed: R51.2, U25.41
unnamed: R52.2, U25.48
unnamed: R53.2, U25.50
unnamed: R54.2, U25.51
unnamed: R55.2, U25.52
unnamed: R56.2, U25.43
unnamed: R57.2, U25.44
unnamed: R58.2, U25.45
unnamed: R59.2, U25.46
unnamed: R60.2, U25.66
unnamed: R61.2, U25.67
unnamed: R62.2, U25.72
unnamed: R63.2, U25.71
unnamed: R64.2, U25.38
unnamed: R65.2, SW1.2, U17.31
unnamed: U26.7, U26.74
unnamed: U26.15, U26.16, U26.33, U26.69
unnamed: U28.5, U31.16
unnamed: U30.4, U31.3
unnamed: U30.5, U31.18
unnamed: U30.6, U31.19
unnamed: U31.26, Y3.3
unnamed: U32.3, Y7.5
unnamed: U32.23, U33.9
unnamed: U32.24, U33.5
unnamed: U32.35, U33.13
unnamed: U32.36, U33.11
unnamed: U32.37, U33.1
unnamed: U32.38, U33.3
RESET: J9.1, U3.F12, U8.13, U17.19, U25.68, U26.59, U28.1, U32.4
RESET_N: J1.B2, J6.B2, J7.B2, U28.2, U31.20
ROM: U17.44, U18.22
RW0: U9.29, U10.29, U13.29, U14.29, U17.48
RW1: U11.29, U12.29, U15.29, U16.29, U17.46
RW_N: J9.23, U3.L3, U8.28, U17.58, U18.31, U22.82, U25.69, U26.57, U31.2, U32.10
SIZ0: U3.L2, U17.5
SIZ1: U3.K3, U17.6
STERM: U3.G1, U17.59
VGA_CS: U17.40, U22.18
VGA_HSYNC: J10.13, U22.97
VGA_VSYNC: J10.14, U22.96
VGB0: U2.18, U22.6
VGB1: U2.17, U22.8
VGB2: U2.16, U22.39
VGB3: U2.15, U22.52
VGB4: U2.14, U22.21
VGB5: U2.13, U22.22
VGB6: U2.12, U22.23
VGB7: U2.11, U22.76
_RW0: U9.24, U10.24, U13.24, U14.24, U17.47
_RW1: U11.24, U12.24, U15.24, U16.24, U17.45
